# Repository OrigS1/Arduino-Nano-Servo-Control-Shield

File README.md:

**ARDUINO NANO SERVO CONTROL SHIELD**

This project is designed to make it easier to control servo motors with an Arduino Nano. With this board, a robotic arm with 4 servos can be controlled.

### BOARD DESİGN

### SCHEMATIC

### PCB PREVİEW

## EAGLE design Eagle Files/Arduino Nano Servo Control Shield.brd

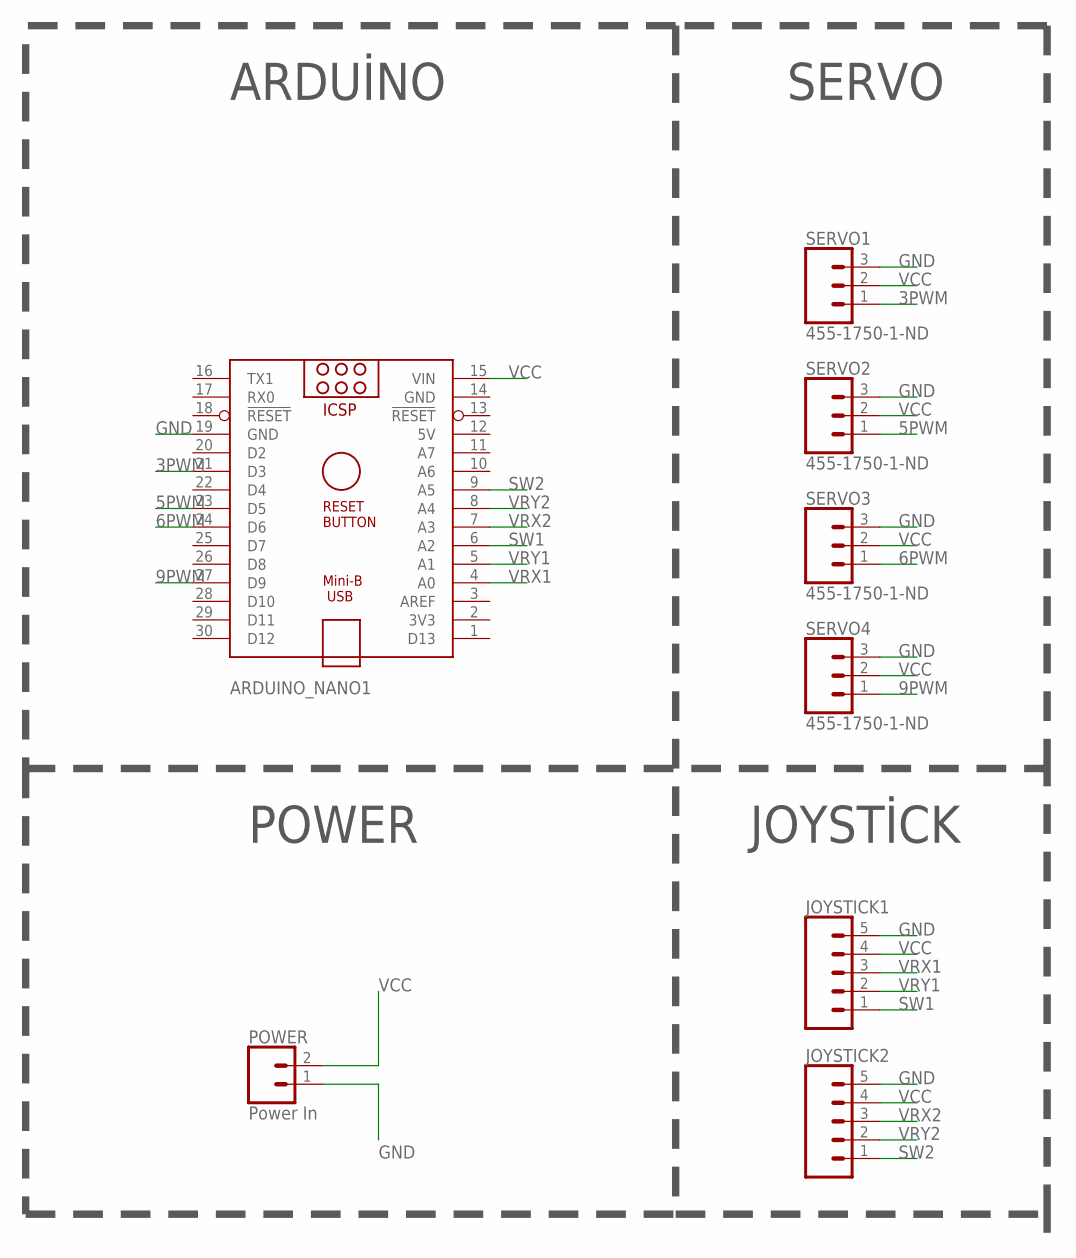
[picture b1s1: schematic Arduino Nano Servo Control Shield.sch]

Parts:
ARDUINO_NANO1: ARDUINO_NANO
JOYSTICK1, JOYSTICK2: CONN_05PTH; 1X05
POWER: Power In; SCREWTERMINAL-3.5MM-2
SERVO1, SERVO2, SERVO3, SERVO4: 455-1750-1-ND; 1X03

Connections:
3PWM: ARDUINO_NANO1.21 (D3), SERVO1.1
5PWM: ARDUINO_NANO1.23 (D5), SERVO2.1
6PWM: ARDUINO_NANO1.24 (D6), SERVO3.1
9PWM: ARDUINO_NANO1.27 (D9), SERVO4.1
GND: ARDUINO_NANO1.14 (GND), ARDUINO_NANO1.19 (GND), JOYSTICK1.5, JOYSTICK2.5, POWER.1, SERVO1.3, SERVO2.3, SERVO3.3, SERVO4.3
SW1: ARDUINO_NANO1.6 (A2), JOYSTICK1.1
SW2: ARDUINO_NANO1.9 (A5), JOYSTICK2.1
VCC: ARDUINO_NANO1.12 (5V), ARDUINO_NANO1.15 (VIN), JOYSTICK1.4, JOYSTICK2.4, POWER.2, SERVO1.2, SERVO2.2, SERVO3.2, SERVO4.2
VRX1: ARDUINO_NANO1.4 (A0), JOYSTICK1.3
VRX2: ARDUINO_NANO1.7 (A3), JOYSTICK2.3
VRY1: ARDUINO_NANO1.5 (A1), JOYSTICK1.2
VRY2: ARDUINO_NANO1.8 (A4), JOYSTICK2.2

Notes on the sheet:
ARDUİNO
SERVO
POWER
JOYSTİCK

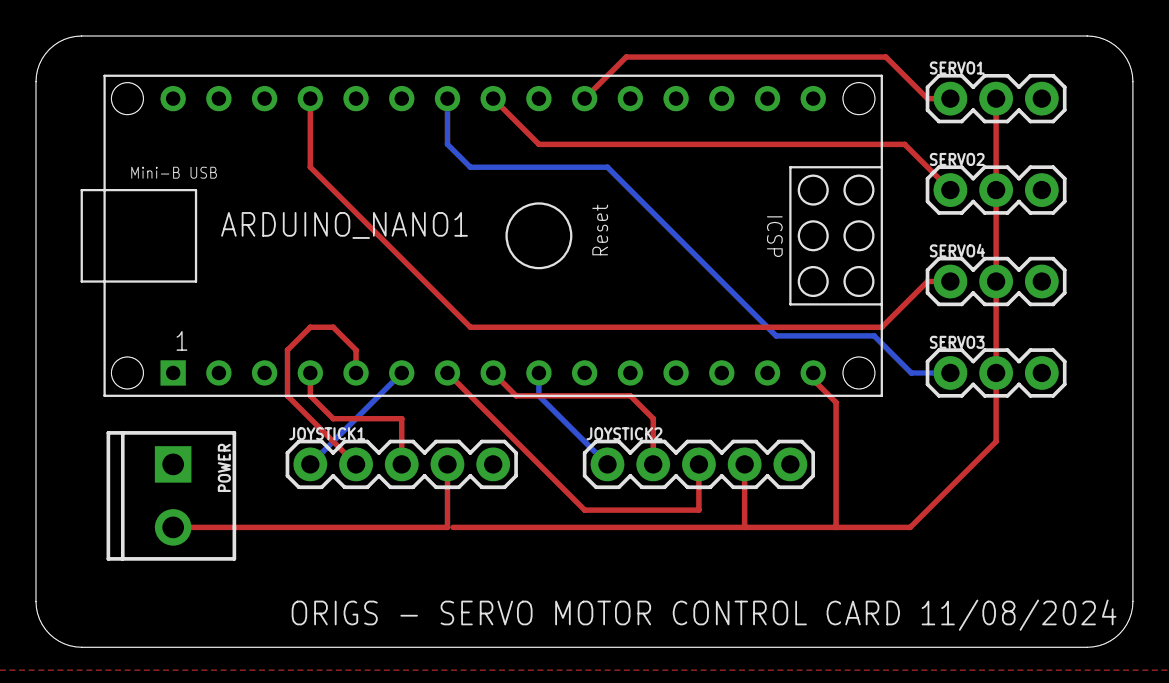
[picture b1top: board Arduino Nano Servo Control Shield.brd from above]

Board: 2 copper layers, 60.9 x 34.0 mm, 8 parts (0 on the bottom side), 12 nets.

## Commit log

2024-08-12 README.md

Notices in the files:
parts and their libraries:
SparkFun-Connectors: Licensing: Creative Commons ShareAlike 4.0 International - https://creativecommons.org/licenses/by-sa/4.0
